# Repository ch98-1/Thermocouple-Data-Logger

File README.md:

# Thermocouple-Data-Logger
Thermocouple Data Logger using MAX31856 and ATmega324PA

Warning: Do not put this device anywhere near lawyers, as it may permanently cease to function if you do so.

**License**

All files are licensed under [zlib license](https://opensource.org/licenses/Zlib) unless noted otherwise.
KiCad Library Files (All .lib .dcm .bck and .pretty files in The Thermocouple-Data-Logger directory) are licensed under [KiCad Libraries License] (http://kicad-pcb.org/libraries/license/)
Petit FatFs Module (All files in /Firmware/pff3) is licensed under Petit FatFs License

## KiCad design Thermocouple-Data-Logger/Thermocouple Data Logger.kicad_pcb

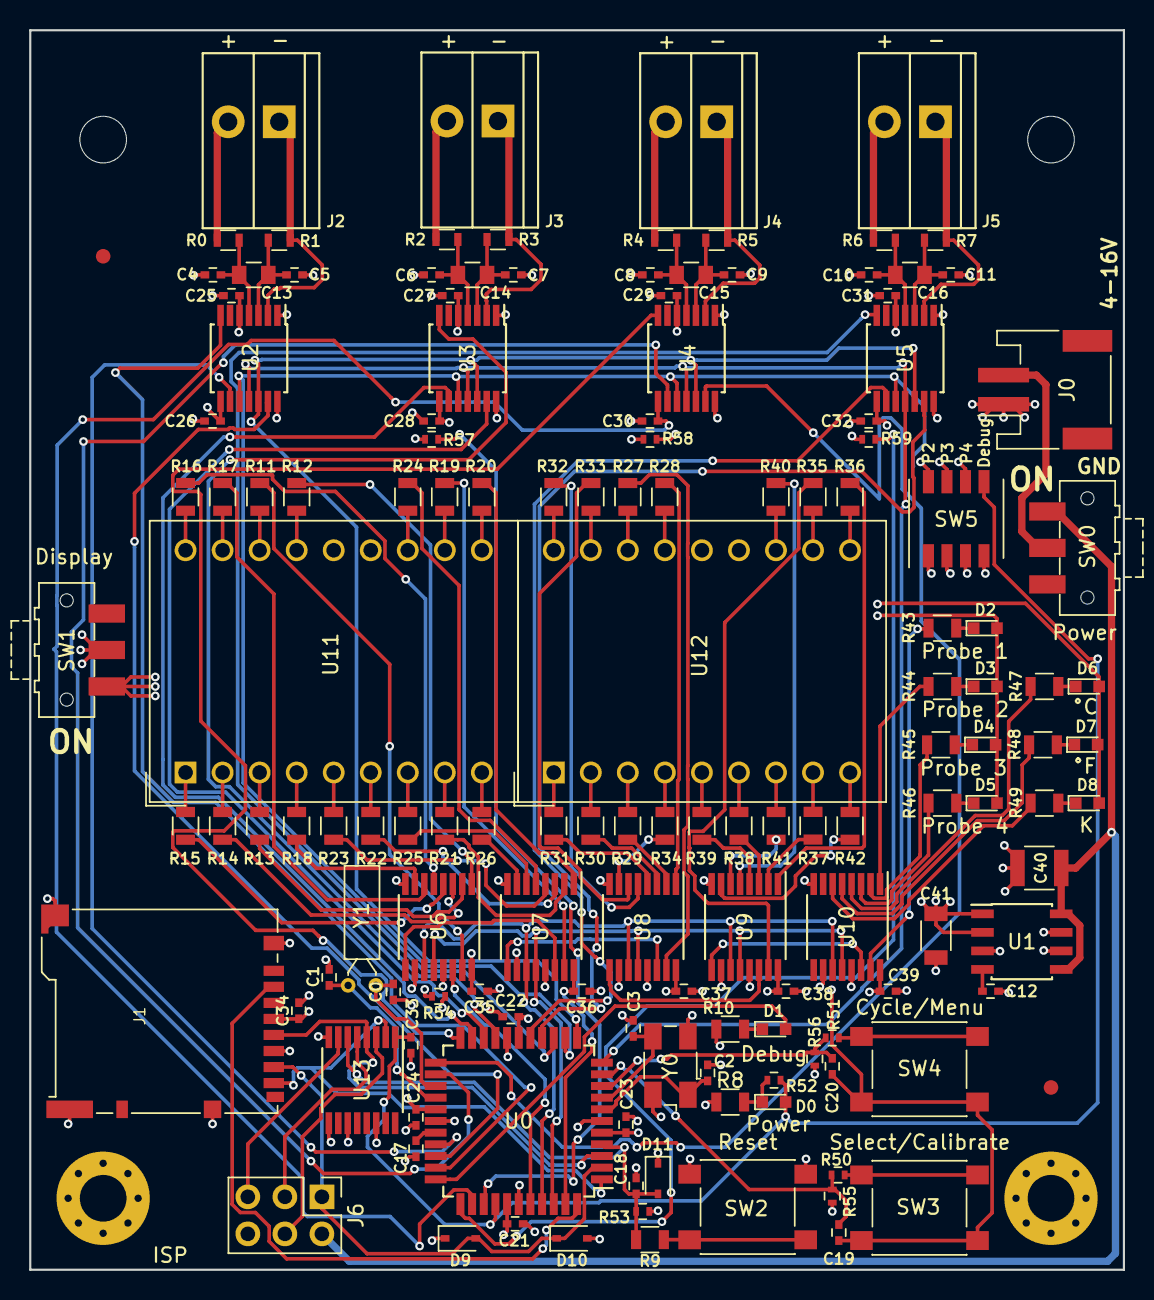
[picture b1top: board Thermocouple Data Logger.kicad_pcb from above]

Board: 4 copper layers, 75.0 x 85.0 mm, 147 parts (0 on the bottom side), 147 nets.

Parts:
C0, C1: 14pF; C_0402
C2, C3: 18pF; C_0402
C4, C5, C6, C7, C8, C9, C10, C11, C12: 0.01uF; C_0402
C13, C14, C15, C16: 0.1uF; C_0805
C17, C18, C19, C20, C21, C22, C23, C24, C25, C26, C27, C28, C29, C30, C31, C32, C33, C34, C35, C36, C37, C38, C39: 0.1uF; C_0402
C40: 10uF; C_1210
C41: 22uf; C_1206
D0: LED Power; LED_0603
D1: LED Debug; LED_0603
D2: LED Probe 1; LED_0603
D3: LED Probe 2; LED_0603
D4: LED Probe 3; LED_0603
D5: LED Probe 4; LED_0603
D6: LED °C; LED_0603
D7: LED °F; LED_0603
D8: LED K; LED_0603
D9, D10, D11: D_Schottky; D_SOD-323
J0: Power; JST_PH_S2B-PH-SM4-TB_02x2.00mm_Angled
J1: Micro_SD_Card_Det; Hirose_DM3BT-DSF-PEJS
J2: Probe 1; TeaminalBlock_Phonix_PTSA-3.5mm_2pol
J3: Probe 2; TeaminalBlock_Phonix_PTSA-3.5mm_2pol
J4: Probe 3; TeaminalBlock_Phonix_PTSA-3.5mm_2pol
J5: Probe 4; TeaminalBlock_Phonix_PTSA-3.5mm_2pol
J6: ISP; Pin_Header_Straight_2x03_Pitch2.54mm
MK0, MK1: Mounting_Hole; MountingHole_3.2mm_M3
MK2, MK3: Mounting_Hole_PAD; MountingHole_3.2mm_M3_Pad_Via
R0, R1, R2, R3, R4, R5, R6, R7: 100; R_0603
R8, R9, R10, R11, R12, R13, R14, R15, R16, R17, R18, R19, R20, R21, R22, R23, R24, R25, R26, R27, R28, R29, R30, R31, R32, R33, R34, R35, R36, R37, R38, R39, R40, R41, R42, R43, R44, R45, R46, R47, R48, R49: 200; R_0805
R50, R51: 1k; R_0402
R52, R53, R54, R55, R56: 10k; R_0402
R57, R58, R59: 470k; R_0402
SW0: Power; SW_SPDT_CK-JS102011SAQN
SW1: Display; SW_SPDT_CK-JS102011SAQN
SW2: Reset; SW_SPST_PTS645
SW3: Select/Calibrate; SW_SPST_PTS645
SW4: Cycle/Menu; SW_SPST_PTS645
SW5: SW_DIP_x04; SW_DIP_x4_W5.08mm_Slide_Copal_CHS-A
U0: ATMEGA324PA-MU; TQFP-44_10x10mm_Pitch0.8mm
U1: LT1763-3.3; SOIC-8_3.9x4.9mm_Pitch1.27mm
U2, U3, U4, U5: MAX31856; TSSOP-14_4.4x5mm_Pitch0.65mm
U6, U7, U8, U9, U10: 74HC595; TSSOP-16_4.4x5mm_Pitch0.65mm
U11, U12: HDSP-521E-Display; HDSP-521E
U13: 4050; TSSOP-16_4.4x5mm_Pitch0.65mm
Y0: 10MHz; Crystal_SMD_Abracon_ABM3B-4pin_5.0x3.2mm
Y1: 32.768KHz; Crystal_DS26_d2.0mm_l6.0mm_Horizontal

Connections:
+3V3: C12.1, C21.1, C22.2, C23.1, C24.2, C25.1, C26.1, C34.2, C41.1, D9.1, D11.1, J1.4, R53.2, SW1.2, SW5.1, SW5.2, SW5.3, SW5.4, U0.5, U0.17, U0.27, U0.38, U1.1, U1.2, U2.5, U2.8
+5V: C40.1, J6.2, SW0.3, U1.5, U1.8
/CLK2/TOSC1: C0.1, U0.25, Y1.1
/CLK2/TOSC2: C1.2, U0.26, Y1.2
/Thermocouple/VCC2: C27.1, C28.1, R57.2, SW5.8, U0.36, U3.5, U3.8
/Thermocouple/VCC3: C29.1, C30.1, R58.2, SW5.7, U0.35, U4.5, U4.8
/Thermocouple/VCC4: C31.1, C32.1, R59.2, SW5.6, U0.34, U5.5, U5.8
CM: C20.2, R51.2, R56.2, U0.9
CS1: U0.30, U2.9
CS2: U0.21, U3.9
CS3: U0.24, U4.9
CS4: U0.16, U5.9
CS5: J1.2, U0.44
DD: C19.1, C20.1, C35.1, C36.1, C37.1, C38.1, C39.1, D2.2, D3.2, D4.2, D5.2, D6.2, D7.2, D8.2, R54.2, SW1.3, SW3.2, SW4.2, U0.43, U6.10, U6.16, U7.10, U7.16, U8.10, U8.16, U9.10, U9.16, U10.10, U10.16, U11.13, U11.14, U12.13, U12.14
DEBUG: C33.2, D0.2, R52.1, SW5.5, U0.37, U13.1
DRDY1: U0.32, U2.7
DRDY2: U0.19, U3.7
DRDY3: U0.22, U4.7
DRDY4: U0.14, U5.7
FAULT1: U0.31, U2.13
FAULT2: U0.20, U3.13
FAULT3: U0.23, U4.13
FAULT4: U0.15, U5.13
GND: C0.2, C1.1, C2.2, C3.2, C4.1, C5.2, C6.1, C7.2, C8.1, C9.2, C10.1, C11.2, C17.2, C18.1, C21.2, C22.1, C23.2, C24.1, C25.2, C26.2, C27.2, C28.2, C29.2, C30.2, C31.2, C32.2, C33.1, C34.1, C35.2, C36.2, C37.2, C38.2, C39.2, C40.2, C41.2, D10.2, J0.1, J1.6, J1.11, J6.6, MK2.1, MK3.1, R8.1, R10.2, R54.1, R55.1, R56.1, R57.1, R58.1, R59.1, SW2.1, U0.6, U0.18, U0.28, U0.39, U1.3, U1.6, U1.7, U2.1, U2.14, U3.1, U3.14, U4.1, U4.14, U5.1, U5.14, U6.8, U6.13, U7.8, U7.13, U8.8, U8.13, U9.8, U9.13, U10.8, U10.13, U13.8, U13.9, U13.11, U13.14, Y0.2, Y0.4
MISO1: D9.2, D10.1, J1.7, J6.1, U0.2
MISO2: U0.11, U2.11, U3.11, U4.11, U5.11
MOSI1: J1.8, U0.1, U13.2
MOSI2: U0.12, U2.12, U3.12, U4.12, U5.12
unnamed: C2.1, U0.7, Y0.1
unnamed: C3.1, U0.8, Y0.3
unnamed: C10.2, C16.1, R6.1, U5.4
unnamed: C11.1, C16.2, R7.1, U5.3
unnamed: C12.2, U1.4
unnamed: C4.2, C13.1, R0.1, U2.4
unnamed: C5.1, C13.2, R1.1, U2.3
unnamed: C6.2, C14.1, R2.1, U3.4
unnamed: C7.1, C14.2, R3.1, U3.3
unnamed: C8.2, C15.1, R4.1, U4.4
unnamed: C9.1, C15.2, R5.1, U4.3
unnamed: C17.1, U0.29
unnamed: D0.1, R8.2, R52.2
unnamed: D1.1, R10.1
unnamed: D1.2, U0.33
unnamed: D2.1, R43.1
unnamed: D3.1, R44.1
unnamed: D4.1, R45.1
unnamed: D5.1, R46.1
unnamed: D6.1, R47.1
unnamed: D7.1, R48.1
unnamed: D8.1, R49.1
unnamed: J0.2, SW0.2
unnamed: J2.1, R1.2, U2.2
unnamed: J2.2, R0.2
unnamed: J3.1, R3.2, U3.2
unnamed: J3.2, R2.2
unnamed: J4.1, R5.2, U4.2
unnamed: J4.2, R4.2
unnamed: J5.1, R7.2, U5.2
unnamed: J5.2, R6.2
unnamed: J6.3, U13.5
unnamed: J6.4, U13.3
unnamed: J6.5, U13.7
unnamed: R9.1, SW2.2
unnamed: R11.1, U11.16
unnamed: R11.2, U6.15
unnamed: R12.1, U11.15
unnamed: R12.2, U6.1
unnamed: R13.1, U11.3
unnamed: R13.2, U6.2
unnamed: R14.1, U11.2
unnamed: R14.2, U6.3
unnamed: R15.1, U11.1
unnamed: R15.2, U6.4
unnamed: R16.1, U11.18
unnamed: R16.2, U6.5
unnamed: R17.1, U11.17
unnamed: R17.2, U6.6
unnamed: R18.1, U11.4
unnamed: R18.2, U6.7
unnamed: R19.1, U7.15
unnamed: R19.2, U11.11
unnamed: R20.1, U7.1
unnamed: R20.2, U11.10
unnamed: R21.1, U7.2
unnamed: R21.2, U11.8
unnamed: R22.1, U7.3
unnamed: R22.2, U11.6
unnamed: R23.1, U7.4
unnamed: R23.2, U11.5
unnamed: R24.1, U7.5
unnamed: R24.2, U11.12
unnamed: R25.1, U7.6
unnamed: R25.2, U11.7
unnamed: R26.1, U7.7
unnamed: R26.2, U11.9
unnamed: R27.1, U12.16
unnamed: R27.2, U8.15
unnamed: R28.1, U12.15
unnamed: R28.2, U8.1
unnamed: R29.1, U12.3
unnamed: R29.2, U8.2
unnamed: R30.1, U12.2
unnamed: R30.2, U8.3
unnamed: R31.1, U12.1
unnamed: R31.2, U8.4
unnamed: R32.1, U12.18
unnamed: R32.2, U8.5
unnamed: R33.1, U12.17
unnamed: R33.2, U8.6
unnamed: R34.1, U12.4
unnamed: R34.2, U8.7
unnamed: R35.1, U9.15
unnamed: R35.2, U12.11
unnamed: R36.1, U9.1
unnamed: R36.2, U12.10
unnamed: R37.1, U9.2
unnamed: R37.2, U12.8
unnamed: R38.1, U9.3
unnamed: R38.2, U12.6
unnamed: R39.1, U9.4
unnamed: R39.2, U12.5
unnamed: R40.1, U9.5
unnamed: R40.2, U12.12
unnamed: R41.1, U9.6
unnamed: R41.2, U12.7
unnamed: R42.1, U9.7
unnamed: R42.2, U12.9
unnamed: R43.2, U10.15
unnamed: R44.2, U10.1
unnamed: R45.2, U10.2
unnamed: R46.2, U10.3
unnamed: R47.2, U10.4
unnamed: R48.2, U10.5
unnamed: R49.2, U10.6
unnamed: R50.1, SW3.1
unnamed: R51.1, SW4.1
QH1: U6.9, U7.14
QH2: U7.9, U8.14
QH3: U8.9, U9.14
QH4: U9.9, U10.14
RCLK: U0.42, U6.12, U7.12, U8.12, U9.12, U10.12
RESET: C18.2, D11.2, R9.2, R53.1, U0.4, U13.6
SC: C19.2, R50.2, R55.2, U0.10
SCK1: J1.5, U0.3, U13.4
SCK2: U0.13, U2.10, U3.10, U4.10, U5.10
SER: U0.40, U6.14
SRCLK: U0.41, U6.11, U7.11, U8.11, U9.11, U10.11

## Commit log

2018-02-15 Created Project Files
2018-02-16 Added more parts
2018-02-16 Changed Voltage Regulator
2018-02-22 More components
2018-02-23 Changed folder name
2018-02-23 Updated License
2018-02-23 Updated License Formatting
2018-02-23 More formatting changes
2018-02-23 Misspelling fixed
2018-02-23 Formatting change
2018-02-23 More formatting
2018-02-27 Added a lot more to the schimatic
2018-02-27 Added the thermocouple module.
2018-02-27 Added switches
2018-02-28 Finished basic schimatic layout
2018-02-28 Updated SD card slot to generic
2018-02-28 Annotated schematic
2018-02-28 Renamed some components
2018-02-28 Made footprint for the terminal block
2018-03-01 Added the components and generaterd the netlist
2018-03-01 Started pcb design
2018-03-01 Imported all the parts
2018-03-01 Started laying out components
2018-03-02 Made thermocouple input layout
2018-03-02 Added mounting holes, grounding holes and fiducials
2018-03-03 Finished general layout of large components
2018-03-06 Changed capacitor values and component layout
2018-03-06 Started laying down traces
2018-03-06 Finished routing all traces
2018-03-06 Centerd board and generated gerber for test view
2018-03-06 Actually generated gerber
2018-03-07 Satrted Labling the Components
2018-03-07 Finished labling the board. Ver 1 hardware
2018-03-07 Gnerated schimatic pdf
2018-03-07 Refilled planes and generated new gerber files
2018-03-08 Generated the BOM from digikey
2018-03-10 Changed licence a bit
2018-03-13 Updated components to something still in stock
2018-03-19 Created fiemware project files and added file system library
2018-03-20 Fixed some silkscreen and added init source file
2018-03-23 Added more test code
2018-04-28 Changed the microcontroller from qfn to tqfp

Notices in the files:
Thermocouple-Data-Logger/Thermocouple Data Logger.kicad_pcb:
(c) 2018 Corwin Hansen
